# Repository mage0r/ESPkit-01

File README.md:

ESPkit-01 - The breakout board for learning ESP-01's
=============

This project is designed as an easy to use adapter to connect your ESP-01 device to a standard serial connection.

Version 1.3 has expanded and now includes a full usb-to-serial chip right on the board.  If you'd prefer the simpiler version, follow this link to [Version 1.2](https://github.com/mage0r/ESPkit-01/tree/v1.2).

It has a program/general use button and a ws2812b to play with some blinky leds.  To enable the ws2812b, simply bridge the "pixel on" pads.

Don't forget to jump on to Andy's github and do the workshop! https://github.com/geekscape/nodemcu_esp8266

[Schematic available here](espkit-01.pdf?raw=true "Schematic")

[Gerber](http://gerblook.org/pcb/zZLnKLdKDrQhMTAEMa8F2Y)

CREDITS
------------

This project was designed by John Spencer and Andy Gelme
You can see our githubs at:
 - https://github.com/mage0r
 - https://github.com/geekscape

Made at hackmelbourne.org!

SPECIAL THANKS
------------

To the HackMelbourne (CCHS, http://hackmelbourne.org) community of Melbourne, Australia.

To all other open-source developers whose countless hours supported every other aspect of this design.

DISTRIBUTION
------------
The specific terms of distribution of this project are governed by the
license referenced below. Please contact the copyright owner if you wish to modify the board for distribution. Please utilize this design for personal or research projects. Please acknowledge all contributors.

LICENSE
-------
Licensed under the TAPR Open Hardware License (www.tapr.org/OHL).
The "license" sub-folder also contains a copy of this license in plain text format.

Copyright John Spencer, Andy Gelme 2016

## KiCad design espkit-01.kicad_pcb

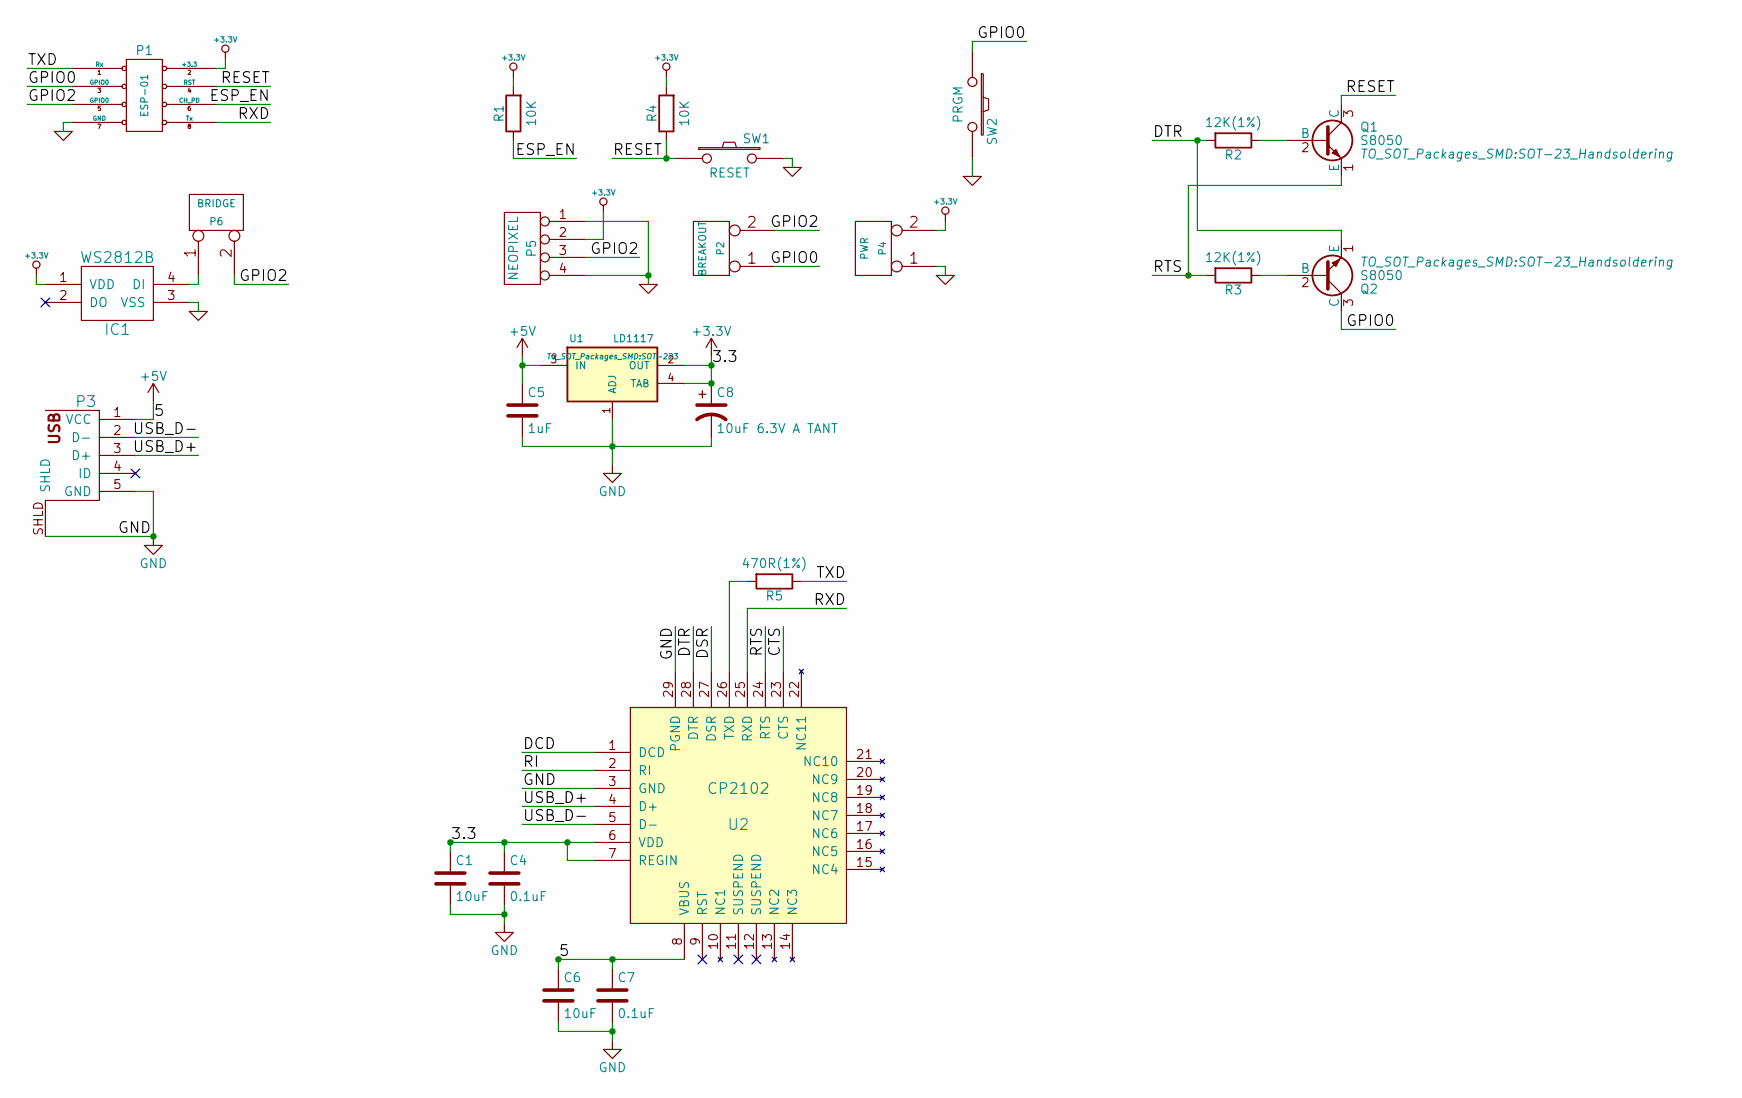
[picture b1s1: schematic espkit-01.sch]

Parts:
C1, C6: 10uF; C_0603_HandSoldering
C4, C7: 0.1uF; C_0603_HandSoldering
C5: 1uF; C_0603_HandSoldering
C8: 10uF 6.3V A TANT; C_0603_HandSoldering
IC1: WS2812B; ws2812b
P1: ESP-01; Pin_Header_Straight_2x04
P2: BREAKOUT; Pin_Header_Straight_1x02
P3: USB_5PIN_SHELL; USB-MICRO-5pin_PTHMOUNT
P4: PWR; Pin_Header_Straight_1x02
P5: NEOPIXEL; Pin_Header_Straight_1x04
P6: BRIDGE; 603_bridge
Q1, Q2: S8050; SOT-23_Handsoldering
R1, R4: 10K; R_0603_HandSoldering
R2, R3: 12K(1%); R_0603_HandSoldering
R5: 470R(1%); R_0603_HandSoldering
SW1: RESET; 1107G
SW2: PRGM; 1107G
U1: LD1117; SOT-223
U2: CP2102; QFN-28-1EP_5x5mm_Pitch0.5mm

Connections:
+5V: C5.1, C6.1, C7.1, P3.1 (VCC), U1.3 (IN), U2.8 (VBUS)
/CTS: U2.23 (CTS)
/DCD: U2.1 (DCD)
/DSR: U2.27 (DSR)
/DTR: Q2.1 (E), R2.2, U2.28 (DTR)
/ESP_EN: P1.6 (CH_PD), R1.1
/GPIO0: P1.3 (GPIO0), P2.1, Q2.3 (C), SW2.1
/GPIO2: P1.5 (GPIO0), P2.2 (PM), P5.3, P6.2 (PM)
/RESET: P1.4 (RST), Q1.3 (C), R4.1, SW1.1
/RI: U2.2 (RI)
/RTS: Q1.1 (E), R3.2, U2.24 (RTS)
/RXD: P1.8 (Tx), U2.25 (RXD)
/TXD: P1.1 (Rx), R5.1
/USB_D+: P3.3 (D+), U2.4 (D+)
/USB_D-: P3.2 (D-), U2.5 (D-)
GND: C1.2, C4.2, C5.2, C6.2, C7.2, C8.2, IC1.3 (VSS), P1.7 (GND), P3.5 (GND), P3.SHLD, P4.1, P5.1, P5.4, SW1.2, SW2.2, U1.1 (ADJ), U2.3 (GND), U2.29 (PGND)
unnamed: IC1.4 (DI), P6.1
unnamed: Q1.2 (B), R2.1
unnamed: Q2.2 (B), R3.1
unnamed: R5.2, U2.26 (TXD)

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
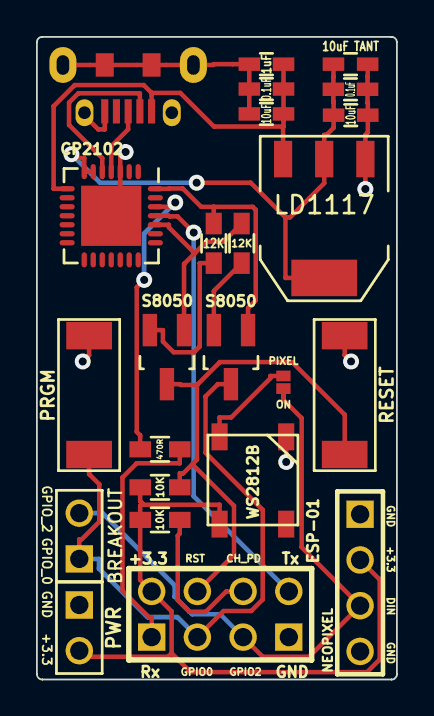
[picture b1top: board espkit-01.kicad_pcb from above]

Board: 2 copper layers, 20.0 x 35.7 mm, 24 parts (0 on the bottom side), 18 nets.

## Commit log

2015-02-27 :tada: Added .gitattributes & .gitignore files
2015-02-28 Added License
2015-02-28 Updated text.
2015-02-28 Added images to readme
2015-03-04 Added Early prototype Photo
2015-03-07 Added single layer version
    or, at least, as single as possible. There are 4 connections on the
    back, but they are between pins.
2015-03-12 Turns out my kinsten gerbers are a bit thin
2015-03-13 Shuffled Layout for 1.1
2015-03-14 Updated board and layout.
2015-05-29 Updated Readme
    How to enable the ws2812b
2015-05-29 Redundant power led removed
    bridge connection now easy to get too.
2016-10-24 New Design with auto program.
    You should be able to do away with the serial/usb programmer and just use the NodeMCU v1.0 board in Arduino to auto-program.
2016-10-24 Updated readme and documentation.
2016-10-24 Sometimes helps to connect your grounds.
